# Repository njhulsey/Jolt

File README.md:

# Jolt

Fall Semester of Sophomore year I was a part of a student organization called Generate which is Northeasterns student-led build studio. Generate works with clients to further their ideas. We provide a semesters worth of free engineering. My time in Generate has been primarily working as a build studio engineer meaning I help bring the client's idea to life. 

Jolt is one of the projects I worked on during my sophomore fall semester. Jolt is a wearable electronic alarm that shocks users awake. Throughout this project I helped build and design the PCB and schematic. I also worked in a team of engineers whom varried in mechanical, electrical, and computer engineering. All of the files I created and worked on can be found in this repository. 

What I learned while working on this project:
  - Interfacing with real time clocks
  - Charging circuits for LiPo batteries
  - PCB conventions
  - Schematic conventions
  - Reading datasheets
  - Picking parts
  - Team communication and effectiveness

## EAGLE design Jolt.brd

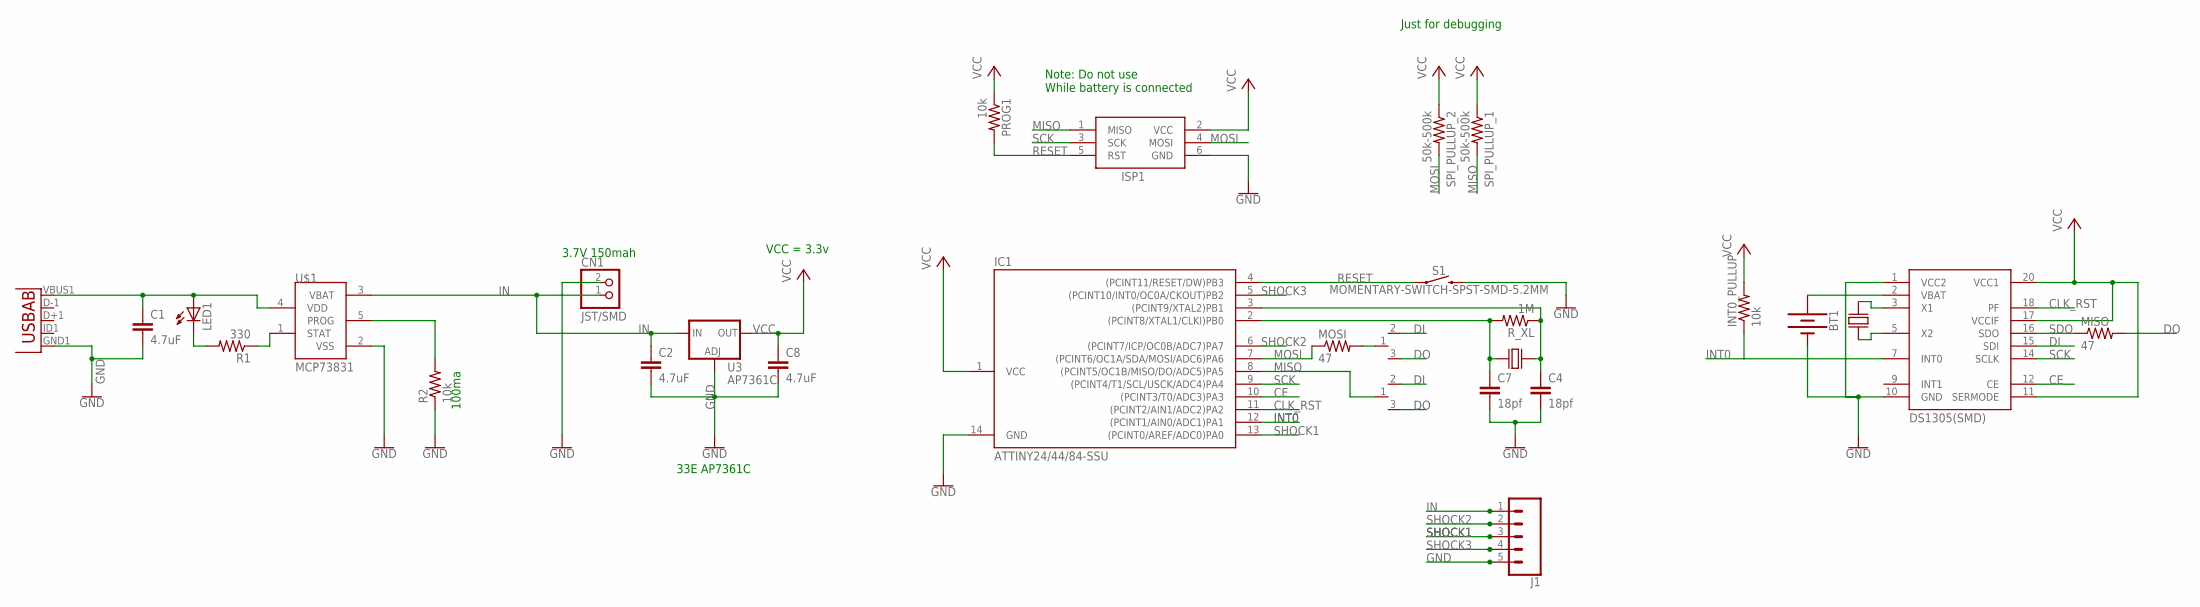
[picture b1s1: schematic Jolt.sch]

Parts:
BT1: BATTERY-20MM_SMD_4LEGS_OVERPASTE; BATTCON_20MM_4LEGS_OVERPASTE
C1, C2, C8: 4.7uF; C0603K
C4, C7: 18pf; 0603
CN1: JST/SMD; JST-PH-2-SMT
IC1: ATTINY24/44/84-SSU; SOIC14
INT0_PULLUP: 10k; R0603
ISP1: AVRISP-6; AVRISP
J1: CONN_05; 1X05
LED1: LEDCHIPLED_0603; CHIPLED_0603
MISO: 47; R0603
MOSI: 47; R0603
PROG1: 10k; R0603
R1: 330; R0603
R2: 10k; R0603
R_XL: 1M; R0603
S1: MOMENTARY-SWITCH-SPST-SMD-5.2MM; TACTILE_SWITCH_SMD_5.2MM
SPI_PULLUP_1, SPI_PULLUP_2: 50k-500k; R0603
U1: USB""; USB-MICRO-SMD
U3: AP7361C; SOT223
U$1: MCP73831; SOT23-5L
U$2: DS1305(SMD); TSSOP
U$3: CRYSTAL_SOJ; SOJ-4-5.5MM
U$4, U$5: 0603_SMD_JUMPER
U$6: CRYSTAL-SMD-HC-49US; CRYSTAL_SMD_HC-49/US

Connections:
CE: IC1.10 ((PCINT3/T0/ADC3)PA3), U$2.12 (CE)
CLK_RST: IC1.11 ((PCINT2/AIN1/ADC2)PA2), U$2.18 (PF)
DI: U$2.15 (SDI), U$4.2 (O2), U$5.2 (O2)
DO: MISO.2, U$4.3 (O1), U$5.3 (O1)
GND: BT1.2 (-), C1.2, C2.2, C4.2, C7.2, C8.2, CN1.2 (1), IC1.14 (GND), ISP1.6 (GND), J1.5, R2.1, S1.3 (2), U1.GND1 (GND), U3.1 (ADJ), U$1.2 (VSS), U$2.1 (VCC2), U$2.10 (GND)
IN: C2.1, CN1.1 (2), J1.1, U3.3 (IN), U$1.3 (VBAT)
INT0: IC1.12 ((PCINT1/AIN0/ADC1)PA1), INT0_PULLUP.1, U$2.7 (INT0)
MISO: IC1.8 ((PCINT5/OC1B/MISO/DO/ADC5)PA5), ISP1.1 (MISO), SPI_PULLUP_1.2, U$5.1 (IN)
MOSI: IC1.7 ((PCINT6/OC1A/SDA/MOSI/ADC6)PA6), ISP1.4 (MOSI), MOSI.1, SPI_PULLUP_2.2
unnamed: C1.1, LED1.A, U1.VBUS1 (VBUS), U$1.4 (VDD)
unnamed: MOSI.2, U$4.1 (IN)
unnamed: R1.1, U$1.1 (STAT)
unnamed: LED1.C, R1.2
unnamed: R2.2, U$1.5 (PROG)
unnamed: C7.1, IC1.2 ((PCINT8/XTAL1/CLKI)PB0), R_XL.2, U$6.P$2
unnamed: C4.1, IC1.3 ((PCINT9/XTAL2)PB1), R_XL.1, U$6.P$1
unnamed: BT1.1 (+), U$2.2 (VBAT)
unnamed: U$2.5 (X2), U$3.P$3
unnamed: U$2.3 (X1), U$3.P$1
RESET: IC1.4 ((PCINT11/RESET/DW)PB3), ISP1.5 (RST), PROG1.2, S1.1
SCK: IC1.9 ((PCINT4/T1/SCL/USCK/ADC4)PA4), ISP1.3 (SCK), U$2.14 (SCLK)
SDO: MISO.1, U$2.16 (SDO)
SHOCK1: IC1.13 ((PCINT0/AREF/ADC0)PA0), J1.3
SHOCK2: IC1.6 ((PCINT7/ICP/OC0B/ADC7)PA7), J1.2
SHOCK3: IC1.5 ((PCINT10/INT0/OC0A/CKOUT)PB2), J1.4
VCC: C8.1, IC1.1 (VCC), INT0_PULLUP.2, ISP1.2 (VCC), PROG1.1, SPI_PULLUP_1.1, SPI_PULLUP_2.1, U3.2 (OUT), U$2.11 (SERMODE), U$2.17 (VCCIF), U$2.20 (VCC1)

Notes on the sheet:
Note: Do not use While battery is connected
VCC = 3.3v
3.7V 150mah
33E AP7361C
100ma
Just for debugging

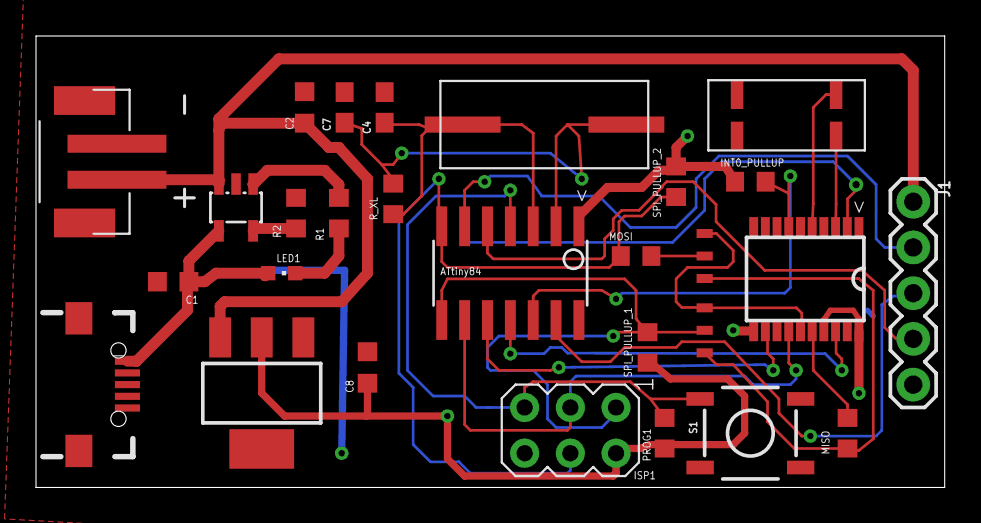
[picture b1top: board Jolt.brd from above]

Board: 2 copper layers, 50.5 x 25.1 mm, 29 parts (1 on the bottom side), 26 nets.

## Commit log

2018-11-09 Create ignore

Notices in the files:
parts and their libraries:
SparkFun-IC-Power: Licensing: Creative Commons ShareAlike 4.0 International - https://creativecommons.org/licenses/by-sa/4.0
